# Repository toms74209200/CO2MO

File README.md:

---

CO2 monitor made with RP2040.

## Devices

- RP2040 development board
- SSD1306 OLED display
- MH-Z19B CO2 sensor

## Schematic

See [RPCM-2111.pdf](pcb/RPCM-2111/RPCM-2111.pdf).

## Build guide

See [build guide](./docs/build_guide_en.md)（[日本語](./docs/build_guide_jp.md)）.

## License

MIT License

## Author

[toms74209200](<https://github.com/toms74209200>)

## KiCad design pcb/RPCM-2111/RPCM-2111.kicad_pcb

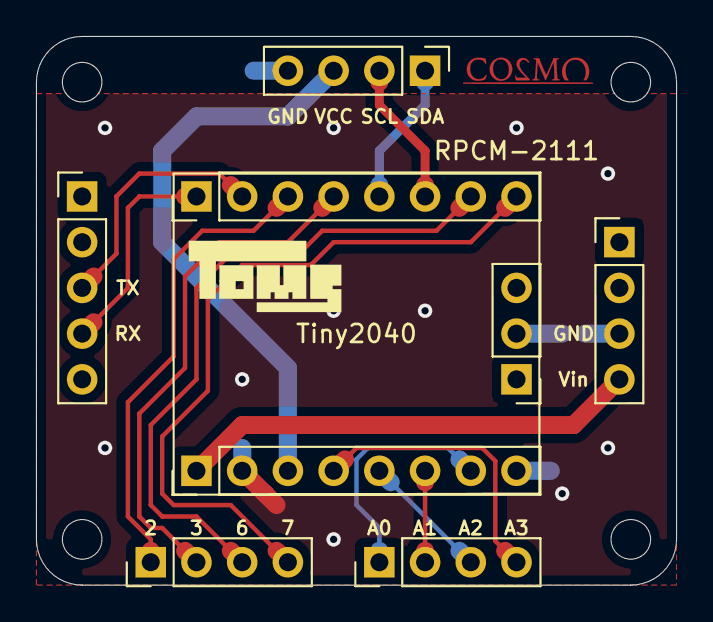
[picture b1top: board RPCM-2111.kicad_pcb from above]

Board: 2 copper layers, 35.6 x 30.5 mm, 8 parts (0 on the bottom side), 15 nets.

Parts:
J1, J2, J5, J8: Conn_01x04_Female; PinHeader_1x04_P2.54mm_Vertical
J3, J4: Conn_01x08_Female; PinHeader_1x08_P2.54mm_Vertical
J6: Conn_01x05_Female; PinHeader_1x05_P2.54mm_Vertical
J7: Conn_01x03_Female; PinHeader_1x03_P2.54mm_Vertical

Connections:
+3V3: J3.3, J8.3
+5V: J3.1, J5.4
/A0: J1.1, J3.7
/A1: J1.2, J3.6
/A2: J1.3, J3.5
/A3: J1.4, J3.4
/GPIO2: J2.1, J4.3
/GPIO3: J2.2, J4.4
/GPIO6: J2.3, J4.7
/GPIO7: J2.4, J4.8
/RX: J4.2, J6.3
/SCL: J4.6, J8.2
/SDA: J4.5, J8.1
/TX: J4.1, J6.4
GND: J3.2, J3.8, J5.3, J7.2, J8.4

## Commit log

2021-10-12 :memo: add TOC of build guide
2021-10-16 :sparkles: add LED blinck code
2021-10-16 :sparkles: add Hello, World! serial port code
2021-10-17 :sparkles: add schematic
2021-10-18 :memo: add header
2021-10-18 :sparkles: add CO2 sensor
2021-10-19 :sparkles: add decoupling capacitors
2021-10-19 :sparkles: add footprint
2021-10-26 :sparkles: add OLED display
2021-10-30 :recycle: clean CO2 sensor library
2021-10-30 :recycle: clean OLED code
2021-10-30 :sparkles: add CO2 monitor
2021-11-01 :sparkles: change schematic
2021-11-02 :sparkles: add labels at wire in schematic
2021-11-02 :memo: add board name
2021-11-02 :sparkles: add PCB layout
2021-11-02 :see_no_evil: add gitignore
2021-11-03 :sparkles: add PCB
2021-11-03 :truck: change PCB project name
2021-11-03 :memo: change README title
2021-11-03 :pencil2: fix comment in schematic
2021-11-03 :recycle: refactor uart module
2021-11-10 :sparkles: add to plot chart
2021-11-11 :sparkles: add util functions of time unit conversion
2021-11-12 :sparkles: add LED controller
2021-11-14 :memo: add learning contents
2021-11-15 :sparkles: add production code
2021-11-16 :sparkles: add initialization of CO2 sensor
2021-11-16 :zap: fix to plot initial data
2021-11-17 :memo: update learning document
2021-11-17 :memo: update build guide
2021-11-21 :memo: add figures in README
2021-11-21 :memo: update documents
2021-11-24 :sparkles: add wakeup image
2021-12-01 :sparkles: add digital filter
2021-12-01 :rewind: revert learning code
2021-12-01 :sparkles: add offset of display data
2021-12-05 :sparkles: fix to panelize
